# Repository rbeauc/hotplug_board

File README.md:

# hotplug_board
Lab board used for hot insertion of battery cells

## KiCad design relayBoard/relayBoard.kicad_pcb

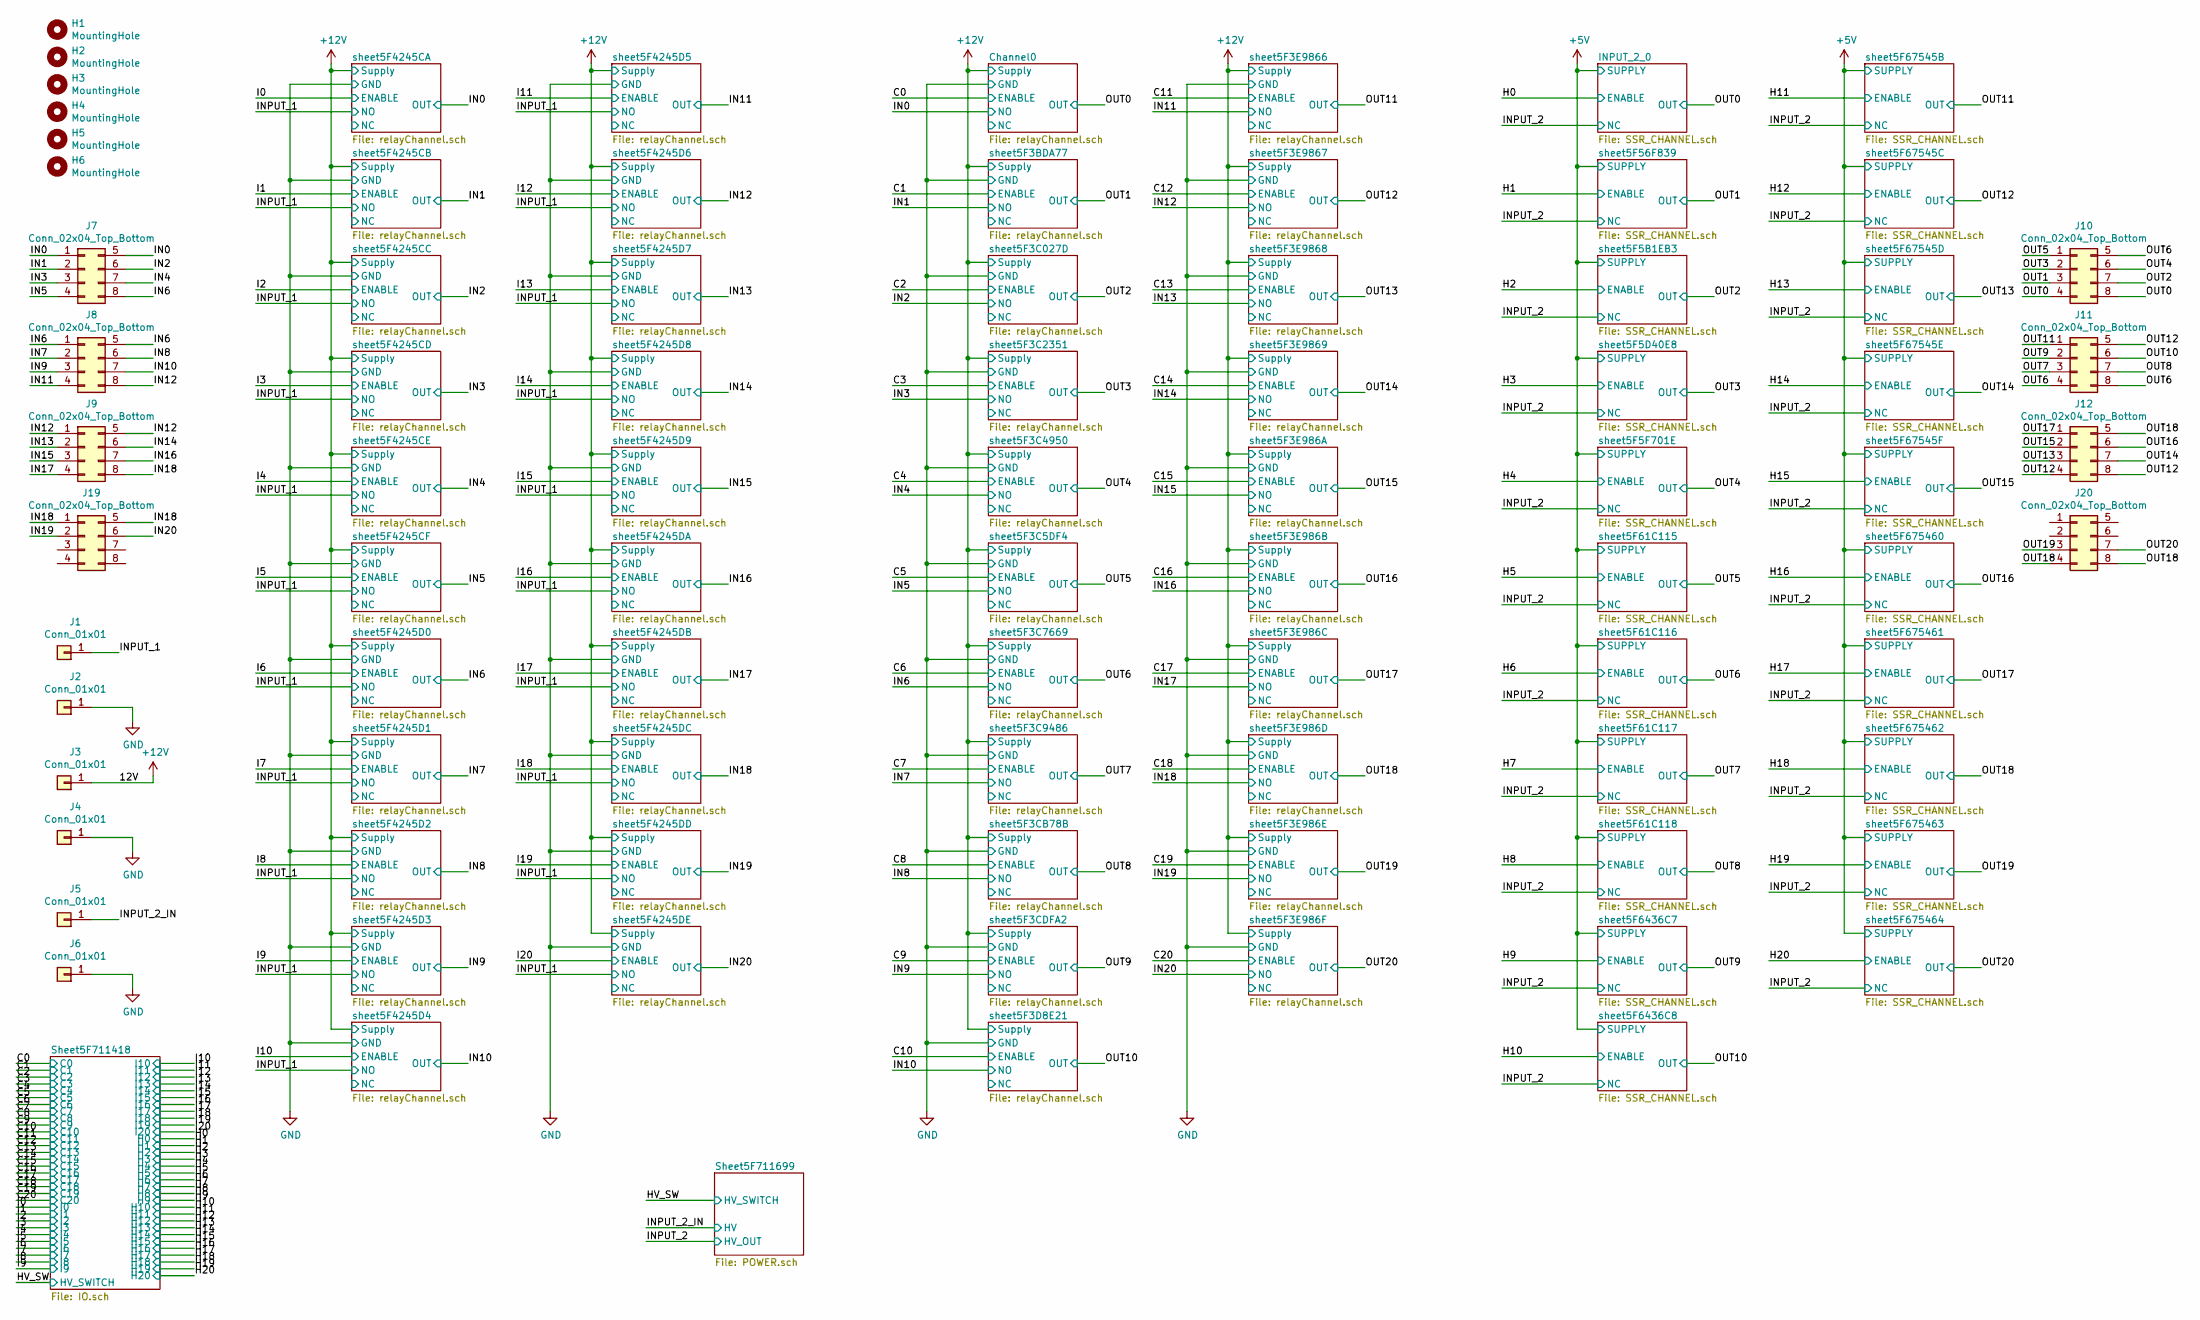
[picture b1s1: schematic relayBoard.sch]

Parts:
H1, H2, H3, H4, H5, H6: MountingHole; MountingHole_5mm
J1, J2, J3, J4, J5, J6: Conn_01x01; Banana_Jack_1Pin
J7, J8, J9, J10, J11, J12, J19, J20: Conn_02x04_Top_Bottom; Molex_Micro-Fit_3.0_43045-0800_2x04_P3.00mm_Horizontal

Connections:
+12V: J3.1; also elsewhere on the board
/IN0: J7.1, J7.5; also elsewhere on the board
/IN1: J7.2; also elsewhere on the board
/IN2: J7.6; also elsewhere on the board
/IN3: J7.3; also elsewhere on the board
/IN4: J7.7; also elsewhere on the board
/IN5: J7.4; also elsewhere on the board
/IN6: J7.8, J8.1, J8.5; also elsewhere on the board
/IN7: J8.2; also elsewhere on the board
/IN8: J8.6; also elsewhere on the board
/IN9: J8.3; also elsewhere on the board
/IN10: J8.7; also elsewhere on the board
/IN11: J8.4; also elsewhere on the board
/IN12: J8.8, J9.1, J9.5; also elsewhere on the board
/IN13: J9.2; also elsewhere on the board
/IN14: J9.6; also elsewhere on the board
/IN15: J9.3; also elsewhere on the board
/IN16: J9.7; also elsewhere on the board
/IN17: J9.4; also elsewhere on the board
/IN18: J9.8, J19.1, J19.5; also elsewhere on the board
/IN19: J19.2; also elsewhere on the board
/IN20: J19.6; also elsewhere on the board
/INPUT_1: J1.1; also elsewhere on the board
/INPUT_2_IN: J5.1; also elsewhere on the board
/OUT0: J10.4, J10.8; also elsewhere on the board
/OUT1: J10.3; also elsewhere on the board
/OUT2: J10.7; also elsewhere on the board
/OUT3: J10.2; also elsewhere on the board
/OUT4: J10.6; also elsewhere on the board
/OUT5: J10.1; also elsewhere on the board
/OUT6: J10.5, J11.4, J11.8; also elsewhere on the board
/OUT7: J11.3; also elsewhere on the board
/OUT8: J11.7; also elsewhere on the board
/OUT9: J11.2; also elsewhere on the board
/OUT10: J11.6; also elsewhere on the board
/OUT11: J11.1; also elsewhere on the board
/OUT12: J11.5, J12.4, J12.8; also elsewhere on the board
/OUT13: J12.3; also elsewhere on the board
/OUT14: J12.7; also elsewhere on the board
/OUT15: J12.2; also elsewhere on the board
/OUT16: J12.6; also elsewhere on the board
/OUT17: J12.1; also elsewhere on the board
/OUT18: J12.5, J20.4, J20.8; also elsewhere on the board
/OUT19: J20.3; also elsewhere on the board
/OUT20: J20.7; also elsewhere on the board
GND: J2.1, J4.1, J6.1; also elsewhere on the board

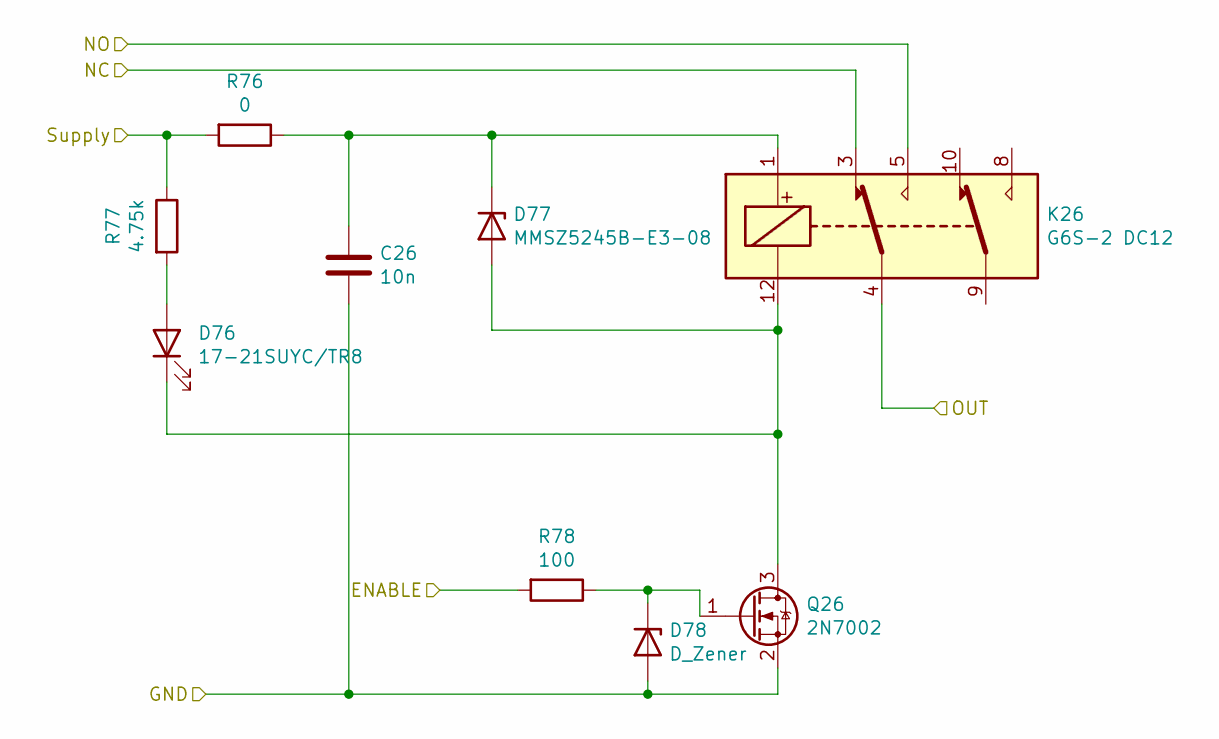
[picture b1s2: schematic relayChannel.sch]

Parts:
C1: 10n; R_0603_1608Metric
D1: 17-21SUYC/TR8; R_0805_2012Metric
D2: MMSZ5245B-E3-08; D_SOD-123
D3: D_Zener; D_0805_2012Metric
K1: G6S-2 DC12; Relay_DPDT_Omron_G6SK-2
Q1: 2N7002; SOT-23
R1: 0; R_0603_1608Metric
R2: 4.75k; R_0603_1608Metric
R3: 100; R_0603_1608Metric

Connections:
+12V: R1.2, R2.1; also elsewhere on the board
/C0: R3.2; also elsewhere on the board
/Channel0/NC: K1.3
/IN0: K1.5; also elsewhere on the board
/OUT0: K1.4; also elsewhere on the board
GND: C1.2, D3.2 (A), Q1.2 (S); also elsewhere on the board
unnamed: C1.1, D2.1 (K), K1.1, R1.1
unnamed: D1.1 (K), D2.2 (A), K1.12, Q1.3 (D)
unnamed: D1.2 (A), R2.2
unnamed: D3.1 (K), Q1.1 (G), R3.1

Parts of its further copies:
C2, C3, C4, C5, C6, C7, C8, C9, C10, C11, C12, C13, C14, C15, C16, C17, C18, C19, C20, C21, C22, C23, C24, C25, C26, C27, C28, C29, C30, C31, C32, C33, C34, C35, C36, C37, C38, C39, C40, C41, C42: 10n; R_0603_1608Metric
D4, D7, D10, D13, D16, D19, D22, D25, D28, D31, D34, D37, D40, D43, D46, D49, D52, D55, D58, D61, D64, D67, D70, D73, D76, D79, D82, D85, D88, D91, D94, D97, D100, D103, D106, D109, D112, D115, D118, D121, D124: 17-21SUYC/TR8; R_0805_2012Metric
D5, D8, D11, D14, D17, D20, D23, D26, D29, D32, D35, D38, D41, D44, D47, D50, D53, D56, D59, D62, D65, D68, D71, D74, D77, D80, D83, D86, D89, D92, D95, D98, D101, D104, D107, D110, D113, D116, D119, D122, D125: MMSZ5245B-E3-08; D_SOD-123
D6, D9, D12, D15, D18, D21, D24, D27, D30, D33, D36, D39, D42, D45, D48, D51, D54, D57, D60, D63, D66, D69, D72, D75, D78, D81, D84, D87, D90, D93, D96, D99, D102, D105, D108, D111, D114, D117, D120, D123, D126: D_Zener; D_0805_2012Metric
K2, K3, K4, K5, K6, K7, K8, K9, K10, K11, K12, K13, K14, K15, K16, K17, K18, K19, K20, K21, K22, K23, K24, K25, K26, K27, K28, K29, K30, K31, K32, K33, K34, K35, K36, K37, K38, K39, K40, K41, K42: G6S-2 DC12; Relay_DPDT_Omron_G6SK-2
Q2, Q3, Q4, Q5, Q6, Q7, Q8, Q9, Q10, Q11, Q12, Q13, Q14, Q15, Q16, Q17, Q18, Q19, Q20, Q21, Q22, Q23, Q24, Q25, Q26, Q27, Q28, Q29, Q30, Q31, Q32, Q33, Q34, Q35, Q36, Q37, Q38, Q39, Q40, Q41, Q42: 2N7002; SOT-23
R5, R8, R11, R14, R17, R20, R23, R26, R29, R32, R35, R38, R41, R44, R47, R50, R53, R56, R59, R62, R65, R68, R71, R74, R77, R80, R83, R86, R89, R92, R95, R98, R101, R104, R107, R110, R113, R116, R119, R122, R125: 4.75k; R_0603_1608Metric
R6, R9, R12, R15, R18, R21, R24, R27, R30, R33, R36, R39, R42, R45, R48, R51, R54, R57, R60, R63, R66, R69, R72, R75, R78, R81, R84, R87, R90, R93, R96, R99, R102, R105, R108, R111, R114, R117, R120, R123, R126: 100; R_0603_1608Metric

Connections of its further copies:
+12V: R5.1, R8.1, R11.1, R14.1, R17.1, R20.1, R23.1, R26.1, R29.1, R32.1, R35.1, R38.1, R41.1, R44.1, R47.1, R50.1, R53.1, R56.1, R59.1, R62.1, R65.1, R68.1, R71.1, R74.1, R77.1, R80.1, R83.1, R86.1, R89.1, R92.1, R95.1, R98.1, R101.1, R104.1, R107.1, R110.1, R113.1, R116.1, R119.1, R122.1, R125.1; also elsewhere on the board
/C1: R6.2; also elsewhere on the board
/C2: R9.2; also elsewhere on the board
/C3: R12.2; also elsewhere on the board
/C4: R15.2; also elsewhere on the board
/C5: R18.2; also elsewhere on the board
/C6: R21.2; also elsewhere on the board
/C7: R24.2; also elsewhere on the board
/C8: R27.2; also elsewhere on the board
/C9: R30.2; also elsewhere on the board
/C10: R33.2; also elsewhere on the board
/C11: R36.2; also elsewhere on the board
/C12: R39.2; also elsewhere on the board
/C13: R42.2; also elsewhere on the board
/C14: R45.2; also elsewhere on the board
/C15: R48.2; also elsewhere on the board
/C16: R51.2; also elsewhere on the board
/C17: R54.2; also elsewhere on the board
/C18: R57.2; also elsewhere on the board
/C19: R60.2; also elsewhere on the board
/C20: R63.2; also elsewhere on the board
/I0: R66.2; also elsewhere on the board
/I1: R69.2; also elsewhere on the board
/I2: R72.2; also elsewhere on the board
/I3: R75.2; also elsewhere on the board
/I4: R78.2; also elsewhere on the board
/I5: R81.2; also elsewhere on the board
/I6: R84.2; also elsewhere on the board
/I7: R87.2; also elsewhere on the board
/I8: R90.2; also elsewhere on the board
/I9: R93.2; also elsewhere on the board
/I10: R96.2; also elsewhere on the board
/I11: R99.2; also elsewhere on the board
/I12: R102.2; also elsewhere on the board
/I13: R105.2; also elsewhere on the board
/I14: R108.2; also elsewhere on the board
/I15: R111.2; also elsewhere on the board
/I16: R114.2; also elsewhere on the board
/I17: R117.2; also elsewhere on the board
/I18: R120.2; also elsewhere on the board
/I19: R123.2; also elsewhere on the board
/I20: R126.2; also elsewhere on the board
/IN0: K22.4; also elsewhere on the board
/IN1: K2.5, K23.4; also elsewhere on the board
/IN2: K3.5, K24.4; also elsewhere on the board
/IN3: K4.5, K25.4; also elsewhere on the board
/IN4: K5.5, K26.4; also elsewhere on the board
/IN5: K6.5, K27.4; also elsewhere on the board
/IN6: K7.5, K28.4; also elsewhere on the board
/IN7: K8.5, K29.4; also elsewhere on the board
/IN8: K9.5, K30.4; also elsewhere on the board
/IN9: K10.5, K31.4; also elsewhere on the board
/IN10: K11.5, K32.4; also elsewhere on the board
/IN11: K12.5, K33.4; also elsewhere on the board
/IN12: K13.5, K34.4; also elsewhere on the board
/IN13: K14.5, K35.4; also elsewhere on the board
/IN14: K15.5, K36.4; also elsewhere on the board
/IN15: K16.5, K37.4; also elsewhere on the board
/IN16: K17.5, K38.4; also elsewhere on the board
/IN17: K18.5, K39.4; also elsewhere on the board
/IN18: K19.5, K40.4; also elsewhere on the board
/IN19: K20.5, K41.4; also elsewhere on the board
/IN20: K21.5, K42.4; also elsewhere on the board
/INPUT_1: K22.5, K23.5, K24.5, K25.5, K26.5, K27.5, K28.5, K29.5, K30.5, K31.5, K32.5, K33.5, K34.5, K35.5, K36.5, K37.5, K38.5, K39.5, K40.5, K41.5, K42.5; also elsewhere on the board
/OUT1: K2.4; also elsewhere on the board
/OUT2: K3.4; also elsewhere on the board
/OUT3: K4.4; also elsewhere on the board
/OUT4: K5.4; also elsewhere on the board
/OUT5: K6.4; also elsewhere on the board
/OUT6: K7.4; also elsewhere on the board
/OUT7: K8.4; also elsewhere on the board
/OUT8: K9.4; also elsewhere on the board
/OUT9: K10.4; also elsewhere on the board
/OUT10: K11.4; also elsewhere on the board
/OUT11: K12.4; also elsewhere on the board
/OUT12: K13.4; also elsewhere on the board
/OUT13: K14.4; also elsewhere on the board
/OUT14: K15.4; also elsewhere on the board
/OUT15: K16.4; also elsewhere on the board
/OUT16: K17.4; also elsewhere on the board
/OUT17: K18.4; also elsewhere on the board
/OUT18: K19.4; also elsewhere on the board
/OUT19: K20.4; also elsewhere on the board
/OUT20: K21.4; also elsewhere on the board
/sheet5F3BDA77/NC: K2.3
/sheet5F3C5DF4/NC: K6.3
/sheet5F3C027D/NC: K3.3
/sheet5F3C2351/NC: K4.3
/sheet5F3C4950/NC: K5.3
/sheet5F3C7669/NC: K7.3
/sheet5F3C9486/NC: K8.3
/sheet5F3CB78B/NC: K9.3
/sheet5F3CDFA2/NC: K10.3
/sheet5F3D8E21/NC: K11.3
/sheet5F3E986A/NC: K16.3
/sheet5F3E986B/NC: K17.3
/sheet5F3E986C/NC: K18.3
/sheet5F3E986D/NC: K19.3
/sheet5F3E986E/NC: K20.3
/sheet5F3E986F/NC: K21.3
/sheet5F3E9866/NC: K12.3
/sheet5F3E9867/NC: K13.3
/sheet5F3E9868/NC: K14.3
/sheet5F3E9869/NC: K15.3
/sheet5F4245CA/NC: K22.3
/sheet5F4245CB/NC: K23.3
/sheet5F4245CC/NC: K24.3
/sheet5F4245CD/NC: K25.3
/sheet5F4245CE/NC: K26.3
/sheet5F4245CF/NC: K27.3
/sheet5F4245D0/NC: K28.3
/sheet5F4245D1/NC: K29.3
/sheet5F4245D2/NC: K30.3
/sheet5F4245D3/NC: K31.3
/sheet5F4245D4/NC: K32.3
/sheet5F4245D5/NC: K33.3
/sheet5F4245D6/NC: K34.3
/sheet5F4245D7/NC: K35.3
/sheet5F4245D8/NC: K36.3
/sheet5F4245D9/NC: K37.3
/sheet5F4245DA/NC: K38.3
/sheet5F4245DB/NC: K39.3
/sheet5F4245DC/NC: K40.3
/sheet5F4245DD/NC: K41.3
/sheet5F4245DE/NC: K42.3
GND: C2.2, C3.2, C4.2, C5.2, C6.2, C7.2, C8.2, C9.2, C10.2, C11.2, C12.2, C13.2, C14.2, C15.2, C16.2, C17.2, C18.2, C19.2, C20.2, C21.2, C22.2, C23.2, C24.2, C25.2, C26.2, C27.2, C28.2, C29.2, C30.2, C31.2, C32.2, C33.2, C34.2, C35.2, C36.2, C37.2, C38.2, C39.2, C40.2, C41.2, C42.2, D6.2 (A), D9.2 (A), D12.2 (A), D15.2 (A), D18.2 (A), D21.2 (A), D24.2 (A), D27.2 (A), D30.2 (A), D33.2 (A), D36.2 (A), D39.2 (A), D42.2 (A), D45.2 (A), D48.2 (A), D51.2 (A), D54.2 (A), D57.2 (A), D60.2 (A), D63.2 (A), D66.2 (A), D69.2 (A), D72.2 (A), D75.2 (A), D78.2 (A), D81.2 (A), D84.2 (A), D87.2 (A), D90.2 (A), D93.2 (A), D96.2 (A), D99.2 (A), D102.2 (A), D105.2 (A), D108.2 (A), D111.2 (A), D114.2 (A), D117.2 (A), D120.2 (A), D123.2 (A), D126.2 (A), Q2.2 (S), Q3.2 (S), Q4.2 (S), Q5.2 (S), Q6.2 (S), Q7.2 (S), Q8.2 (S), Q9.2 (S), Q10.2 (S), Q11.2 (S), Q12.2 (S), Q13.2 (S), Q14.2 (S), Q15.2 (S), Q16.2 (S), Q17.2 (S), Q18.2 (S), Q19.2 (S), Q20.2 (S), Q21.2 (S), Q22.2 (S), Q23.2 (S), Q24.2 (S), Q25.2 (S), Q26.2 (S), Q27.2 (S), Q28.2 (S), Q29.2 (S), Q30.2 (S), Q31.2 (S), Q32.2 (S), Q33.2 (S), Q34.2 (S), Q35.2 (S), Q36.2 (S), Q37.2 (S), Q38.2 (S), Q39.2 (S), Q40.2 (S), Q41.2 (S), Q42.2 (S); also elsewhere on the board
unnamed 162: C2.1, D5.1 (K), K2.1; also elsewhere on the board
unnamed 163: C3.1, D8.1 (K), K3.1; also elsewhere on the board
unnamed 164: C4.1, D11.1 (K), K4.1; also elsewhere on the board
unnamed 165: C5.1, D14.1 (K), K5.1; also elsewhere on the board
unnamed 166: C6.1, D17.1 (K), K6.1; also elsewhere on the board
unnamed 167: C7.1, D20.1 (K), K7.1; also elsewhere on the board
unnamed 168: C8.1, D23.1 (K), K8.1; also elsewhere on the board
unnamed 169: C9.1, D26.1 (K), K9.1; also elsewhere on the board
unnamed 170: C10.1, D29.1 (K), K10.1; also elsewhere on the board
unnamed 171: C11.1, D32.1 (K), K11.1; also elsewhere on the board
unnamed 172: C12.1, D35.1 (K), K12.1; also elsewhere on the board
unnamed 173: C13.1, D38.1 (K), K13.1; also elsewhere on the board
unnamed 174: C14.1, D41.1 (K), K14.1; also elsewhere on the board
unnamed 175: C15.1, D44.1 (K), K15.1; also elsewhere on the board
unnamed 176: C16.1, D47.1 (K), K16.1; also elsewhere on the board
unnamed 177: C17.1, D50.1 (K), K17.1; also elsewhere on the board
unnamed 178: C18.1, D53.1 (K), K18.1; also elsewhere on the board
unnamed 179: C19.1, D56.1 (K), K19.1; also elsewhere on the board
unnamed 180: C20.1, D59.1 (K), K20.1; also elsewhere on the board
unnamed 181: C21.1, D62.1 (K), K21.1; also elsewhere on the board
unnamed 182: C22.1, D65.1 (K), K22.1; also elsewhere on the board
unnamed 183: C23.1, D68.1 (K), K23.1; also elsewhere on the board
unnamed 184: C24.1, D71.1 (K), K24.1; also elsewhere on the board
unnamed 185: C25.1, D74.1 (K), K25.1; also elsewhere on the board
unnamed 186: C26.1, D77.1 (K), K26.1; also elsewhere on the board
unnamed 187: C27.1, D80.1 (K), K27.1; also elsewhere on the board
unnamed 188: C28.1, D83.1 (K), K28.1; also elsewhere on the board
unnamed 189: C29.1, D86.1 (K), K29.1; also elsewhere on the board
unnamed 190: C30.1, D89.1 (K), K30.1; also elsewhere on the board
unnamed 191: C31.1, D92.1 (K), K31.1; also elsewhere on the board
unnamed 192: C32.1, D95.1 (K), K32.1; also elsewhere on the board
unnamed 193: C33.1, D98.1 (K), K33.1; also elsewhere on the board
unnamed 194: C34.1, D101.1 (K), K34.1; also elsewhere on the board
unnamed 195: C35.1, D104.1 (K), K35.1; also elsewhere on the board
unnamed 196: C36.1, D107.1 (K), K36.1; also elsewhere on the board
unnamed 197: C37.1, D110.1 (K), K37.1; also elsewhere on the board
unnamed 198: C38.1, D113.1 (K), K38.1; also elsewhere on the board
unnamed 199: C39.1, D116.1 (K), K39.1; also elsewhere on the board
unnamed 200: C40.1, D119.1 (K), K40.1; also elsewhere on the board
unnamed 201: C41.1, D122.1 (K), K41.1; also elsewhere on the board
unnamed 202: C42.1, D125.1 (K), K42.1; also elsewhere on the board
unnamed: D4.1 (K), D5.2 (A), K2.12, Q2.3 (D)
unnamed: D4.2 (A), R5.2
unnamed: D6.1 (K), Q2.1 (G), R6.1
unnamed: D7.1 (K), D8.2 (A), K3.12, Q3.3 (D)
unnamed: D7.2 (A), R8.2
unnamed: D9.1 (K), Q3.1 (G), R9.1
unnamed: D10.1 (K), D11.2 (A), K4.12, Q4.3 (D)
unnamed: D10.2 (A), R11.2
unnamed: D12.1 (K), Q4.1 (G), R12.1
unnamed: D13.1 (K), D14.2 (A), K5.12, Q5.3 (D)
unnamed: D13.2 (A), R14.2
unnamed: D15.1 (K), Q5.1 (G), R15.1
unnamed: D16.1 (K), D17.2 (A), K6.12, Q6.3 (D)
unnamed: D16.2 (A), R17.2
unnamed: D18.1 (K), Q6.1 (G), R18.1
unnamed: D19.1 (K), D20.2 (A), K7.12, Q7.3 (D)
unnamed: D19.2 (A), R20.2
unnamed: D21.1 (K), Q7.1 (G), R21.1
unnamed: D22.1 (K), D23.2 (A), K8.12, Q8.3 (D)
unnamed: D22.2 (A), R23.2
unnamed: D24.1 (K), Q8.1 (G), R24.1
unnamed: D25.1 (K), D26.2 (A), K9.12, Q9.3 (D)
unnamed: D25.2 (A), R26.2
unnamed: D27.1 (K), Q9.1 (G), R27.1
unnamed: D28.1 (K), D29.2 (A), K10.12, Q10.3 (D)
unnamed: D28.2 (A), R29.2
unnamed: D30.1 (K), Q10.1 (G), R30.1
unnamed: D31.1 (K), D32.2 (A), K11.12, Q11.3 (D)
unnamed: D31.2 (A), R32.2
unnamed: D33.1 (K), Q11.1 (G), R33.1
unnamed: D34.1 (K), D35.2 (A), K12.12, Q12.3 (D)
unnamed: D34.2 (A), R35.2
unnamed: D36.1 (K), Q12.1 (G), R36.1
unnamed: D37.1 (K), D38.2 (A), K13.12, Q13.3 (D)
unnamed: D37.2 (A), R38.2
unnamed: D39.1 (K), Q13.1 (G), R39.1
unnamed: D40.1 (K), D41.2 (A), K14.12, Q14.3 (D)
unnamed: D40.2 (A), R41.2
unnamed: D42.1 (K), Q14.1 (G), R42.1
unnamed: D43.1 (K), D44.2 (A), K15.12, Q15.3 (D)
unnamed: D43.2 (A), R44.2
unnamed: D45.1 (K), Q15.1 (G), R45.1
unnamed: D46.1 (K), D47.2 (A), K16.12, Q16.3 (D)
unnamed: D46.2 (A), R47.2
unnamed: D48.1 (K), Q16.1 (G), R48.1
unnamed: D49.1 (K), D50.2 (A), K17.12, Q17.3 (D)
unnamed: D49.2 (A), R50.2
unnamed: D51.1 (K), Q17.1 (G), R51.1
unnamed: D52.1 (K), D53.2 (A), K18.12, Q18.3 (D)
unnamed: D52.2 (A), R53.2
unnamed: D54.1 (K), Q18.1 (G), R54.1
unnamed: D55.1 (K), D56.2 (A), K19.12, Q19.3 (D)
unnamed: D55.2 (A), R56.2
unnamed: D57.1 (K), Q19.1 (G), R57.1
unnamed: D58.1 (K), D59.2 (A), K20.12, Q20.3 (D)
unnamed: D58.2 (A), R59.2
unnamed: D60.1 (K), Q20.1 (G), R60.1
unnamed: D61.1 (K), D62.2 (A), K21.12, Q21.3 (D)
unnamed: D61.2 (A), R62.2
unnamed: D63.1 (K), Q21.1 (G), R63.1
unnamed: D64.1 (K), D65.2 (A), K22.12, Q22.3 (D)
unnamed: D64.2 (A), R65.2
unnamed: D66.1 (K), Q22.1 (G), R66.1
unnamed: D67.1 (K), D68.2 (A), K23.12, Q23.3 (D)
unnamed: D67.2 (A), R68.2
unnamed: D69.1 (K), Q23.1 (G), R69.1
unnamed: D70.1 (K), D71.2 (A), K24.12, Q24.3 (D)
unnamed: D70.2 (A), R71.2
unnamed: D72.1 (K), Q24.1 (G), R72.1
unnamed: D73.1 (K), D74.2 (A), K25.12, Q25.3 (D)
unnamed: D73.2 (A), R74.2
unnamed: D75.1 (K), Q25.1 (G), R75.1
unnamed: D76.1 (K), D77.2 (A), K26.12, Q26.3 (D)
unnamed: D76.2 (A), R77.2
unnamed: D78.1 (K), Q26.1 (G), R78.1
unnamed: D79.1 (K), D80.2 (A), K27.12, Q27.3 (D)
unnamed: D79.2 (A), R80.2
unnamed: D81.1 (K), Q27.1 (G), R81.1
unnamed: D82.1 (K), D83.2 (A), K28.12, Q28.3 (D)
unnamed: D82.2 (A), R83.2
unnamed: D84.1 (K), Q28.1 (G), R84.1
unnamed: D85.1 (K), D86.2 (A), K29.12, Q29.3 (D)
unnamed: D85.2 (A), R86.2
unnamed: D87.1 (K), Q29.1 (G), R87.1
unnamed: D88.1 (K), D89.2 (A), K30.12, Q30.3 (D)
unnamed: D88.2 (A), R89.2
unnamed: D90.1 (K), Q30.1 (G), R90.1
unnamed: D91.1 (K), D92.2 (A), K31.12, Q31.3 (D)
unnamed: D91.2 (A), R92.2
unnamed: D93.1 (K), Q31.1 (G), R93.1
unnamed: D94.1 (K), D95.2 (A), K32.12, Q32.3 (D)
unnamed: D94.2 (A), R95.2
unnamed: D96.1 (K), Q32.1 (G), R96.1
unnamed: D97.1 (K), D98.2 (A), K33.12, Q33.3 (D)
unnamed: D97.2 (A), R98.2
unnamed: D99.1 (K), Q33.1 (G), R99.1
unnamed: D100.1 (K), D101.2 (A), K34.12, Q34.3 (D)
unnamed: D100.2 (A), R101.2
unnamed: D102.1 (K), Q34.1 (G), R102.1
unnamed: D103.1 (K), D104.2 (A), K35.12, Q35.3 (D)
unnamed: D103.2 (A), R104.2
unnamed: D105.1 (K), Q35.1 (G), R105.1
unnamed: D106.1 (K), D107.2 (A), K36.12, Q36.3 (D)
unnamed: D106.2 (A), R107.2
unnamed: D108.1 (K), Q36.1 (G), R108.1
unnamed: D109.1 (K), D110.2 (A), K37.12, Q37.3 (D)
unnamed: D109.2 (A), R110.2
unnamed: D111.1 (K), Q37.1 (G), R111.1
unnamed: D112.1 (K), D113.2 (A), K38.12, Q38.3 (D)
unnamed: D112.2 (A), R113.2
unnamed: D114.1 (K), Q38.1 (G), R114.1
unnamed: D115.1 (K), D116.2 (A), K39.12, Q39.3 (D)
unnamed: D115.2 (A), R116.2
unnamed: D117.1 (K), Q39.1 (G), R117.1
unnamed: D118.1 (K), D119.2 (A), K40.12, Q40.3 (D)
unnamed: D118.2 (A), R119.2
unnamed: D120.1 (K), Q40.1 (G), R120.1
unnamed: D121.1 (K), D122.2 (A), K41.12, Q41.3 (D)
unnamed: D121.2 (A), R122.2
unnamed: D123.1 (K), Q41.1 (G), R123.1
unnamed: D124.1 (K), D125.2 (A), K42.12, Q42.3 (D)
unnamed: D124.2 (A), R125.2
unnamed: D126.1 (K), Q42.1 (G), R126.1

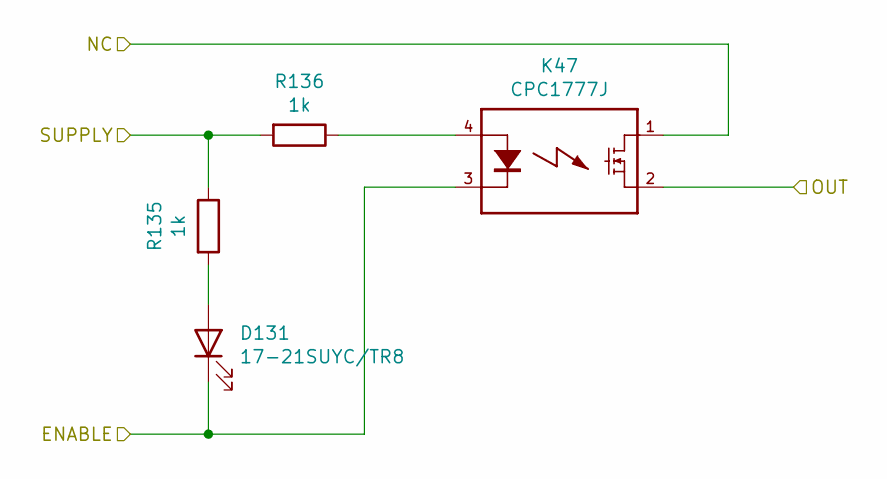
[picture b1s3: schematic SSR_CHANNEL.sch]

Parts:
D127: 17-21SUYC/TR8; R_0805_2012Metric
K43: CPC1777J; TO381P2016X515X2916-4
R127, R128: 1k; R_0603_1608Metric

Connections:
+5V: R127.1, R128.2; also elsewhere on the board
/H0: D127.1 (K), K43.3; also elsewhere on the board
/OUT0: K43.2; also elsewhere on the board
unnamed: D127.2 (A), R127.2
unnamed: K43.4, R128.1

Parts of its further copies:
D128, D129, D130, D131, D132, D133, D134, D135, D136, D137, D138, D139, D140, D141, D142, D143, D144, D145, D146, D147: 17-21SUYC/TR8; R_0805_2012Metric
K44, K45, K46, K47, K48, K49, K50, K51, K52, K53, K54, K55, K56, K57, K58, K59, K60, K61, K62, K63: CPC1777J; TO381P2016X515X2916-4
R129, R130, R131, R132, R133, R134, R135, R136, R137, R138, R139, R140, R141, R142, R143, R144, R145, R146, R147, R148, R149, R150, R151, R152, R153, R154, R155, R156, R157, R158, R159, R160, R161, R162, R163, R164, R165, R166, R167, R168: 1k; R_0603_1608Metric

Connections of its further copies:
+5V: R129.1, R130.2, R131.1, R132.2, R133.1, R134.2, R135.1, R136.2, R137.1, R138.2, R139.1, R140.2, R141.1, R142.2, R143.1, R144.2, R145.1, R146.2, R147.1, R148.2, R149.1, R150.2, R151.1, R152.2, R153.1, R154.2, R155.1, R156.2, R157.1, R158.2, R159.1, R160.2, R161.1, R162.2, R163.1, R164.2, R165.1, R166.2, R167.1, R168.2; also elsewhere on the board
/H1: D128.1 (K), K44.3; also elsewhere on the board
/H2: D129.1 (K), K45.3; also elsewhere on the board
/H3: D130.1 (K), K46.3; also elsewhere on the board
/H4: D131.1 (K), K47.3; also elsewhere on the board
/H5: D132.1 (K), K48.3; also elsewhere on the board
/H6: D133.1 (K), K49.3; also elsewhere on the board
/H7: D134.1 (K), K50.3; also elsewhere on the board
/H8: D135.1 (K), K51.3; also elsewhere on the board
/H9: D136.1 (K), K52.3; also elsewhere on the board
/H10: D137.1 (K), K53.3; also elsewhere on the board
/H11: D138.1 (K), K54.3; also elsewhere on the board
/H12: D139.1 (K), K55.3; also elsewhere on the board
/H13: D140.1 (K), K56.3; also elsewhere on the board
/H14: D141.1 (K), K57.3; also elsewhere on the board
/H15: D142.1 (K), K58.3; also elsewhere on the board
/H16: D143.1 (K), K59.3; also elsewhere on the board
/H17: D144.1 (K), K60.3; also elsewhere on the board
/H18: D145.1 (K), K61.3; also elsewhere on the board
/H19: D146.1 (K), K62.3; also elsewhere on the board
/H20: D147.1 (K), K63.3; also elsewhere on the board
/OUT1: K44.2; also elsewhere on the board
/OUT2: K45.2; also elsewhere on the board
/OUT3: K46.2; also elsewhere on the board
/OUT4: K47.2; also elsewhere on the board
/OUT5: K48.2; also elsewhere on the board
/OUT6: K49.2; also elsewhere on the board
/OUT7: K50.2; also elsewhere on the board
/OUT8: K51.2; also elsewhere on the board
/OUT9: K52.2; also elsewhere on the board
/OUT10: K53.2; also elsewhere on the board
/OUT11: K54.2; also elsewhere on the board
/OUT12: K55.2; also elsewhere on the board
/OUT13: K56.2; also elsewhere on the board
/OUT14: K57.2; also elsewhere on the board
/OUT15: K58.2; also elsewhere on the board
/OUT16: K59.2; also elsewhere on the board
/OUT17: K60.2; also elsewhere on the board
/OUT18: K61.2; also elsewhere on the board
/OUT19: K62.2; also elsewhere on the board
/OUT20: K63.2; also elsewhere on the board
unnamed: D128.2 (A), R129.2
unnamed: D129.2 (A), R131.2
unnamed: D130.2 (A), R133.2
unnamed: D131.2 (A), R135.2
unnamed: D132.2 (A), R137.2
unnamed: D133.2 (A), R139.2
unnamed: D134.2 (A), R141.2
unnamed: D135.2 (A), R143.2
unnamed: D136.2 (A), R145.2
unnamed: D137.2 (A), R147.2
unnamed: D138.2 (A), R149.2
unnamed: D139.2 (A), R151.2
unnamed: D140.2 (A), R153.2
unnamed: D141.2 (A), R155.2
unnamed: D142.2 (A), R157.2
unnamed: D143.2 (A), R159.2
unnamed: D144.2 (A), R161.2
unnamed: D145.2 (A), R163.2
unnamed: D146.2 (A), R165.2
unnamed: D147.2 (A), R167.2
unnamed: K44.4, R130.1
unnamed: K45.4, R132.1
unnamed: K46.4, R134.1
unnamed: K47.4, R136.1
unnamed: K48.4, R138.1
unnamed: K49.4, R140.1
unnamed: K50.4, R142.1
unnamed: K51.4, R144.1
unnamed: K52.4, R146.1
unnamed: K53.4, R148.1
unnamed: K54.4, R150.1
unnamed: K55.4, R152.1
unnamed: K56.4, R154.1
unnamed: K57.4, R156.1
unnamed: K58.4, R158.1
unnamed: K59.4, R160.1
unnamed: K60.4, R162.1
unnamed: K61.4, R164.1
unnamed: K62.4, R166.1
unnamed: K63.4, R168.1

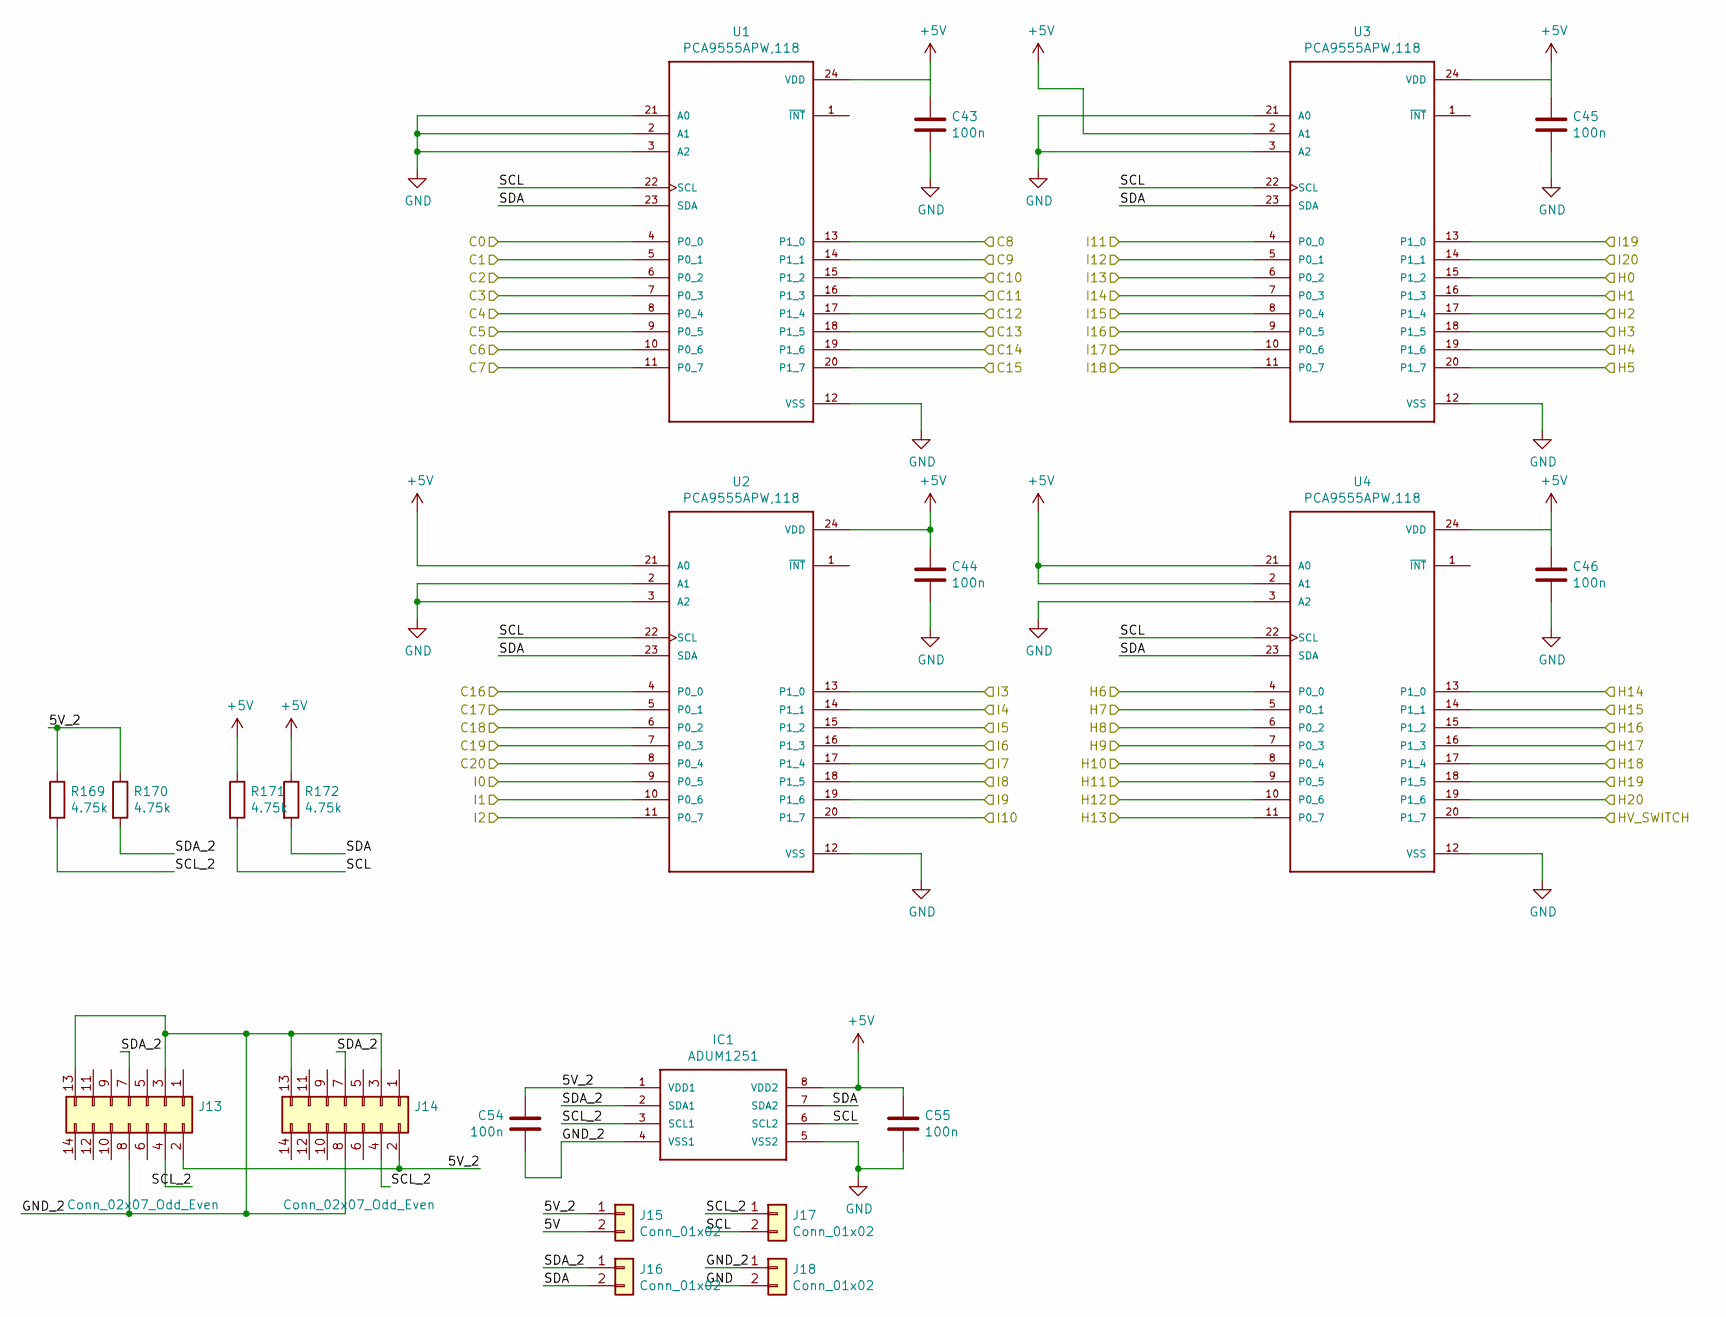
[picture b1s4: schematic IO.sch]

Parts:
C43, C44, C45, C46, C54, C55: 100n; R_0603_1608Metric
IC1: ADUM1251; SO08
J13, J14: Conn_02x07_Odd_Even; PinHeader_2x07_P2.00mm_Vertical
J15, J16, J17, J18: Conn_01x02; PinHeader_1x02_P2.00mm_Vertical
R169, R170, R171, R172: 4.75k; R_0603_1608Metric
U1, U2, U3, U4: PCA9555APW,118; SOP65P640X110-24N

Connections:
+5V: C43.1, C44.1, C45.1, C46.1, C55.1, IC1.8 (VDD2), R171.1, R172.1, U1.24 (VDD), U2.21 (A0), U2.24 (VDD), U3.2 (A1), U3.24 (VDD), U4.2 (A1), U4.21 (A0), U4.24 (VDD); also elsewhere on the board
/C0: U1.4 (P0_0); also elsewhere on the board
/C1: U1.5 (P0_1); also elsewhere on the board
/C2: U1.6 (P0_2); also elsewhere on the board
/C3: U1.7 (P0_3); also elsewhere on the board
/C4: U1.8 (P0_4); also elsewhere on the board
/C5: U1.9 (P0_5); also elsewhere on the board
/C6: U1.10 (P0_6); also elsewhere on the board
/C7: U1.11 (P0_7); also elsewhere on the board
/C8: U1.13 (P1_0); also elsewhere on the board
/C9: U1.14 (P1_1); also elsewhere on the board
/C10: U1.15 (P1_2); also elsewhere on the board
/C11: U1.16 (P1_3); also elsewhere on the board
/C12: U1.17 (P1_4); also elsewhere on the board
/C13: U1.18 (P1_5); also elsewhere on the board
/C14: U1.19 (P1_6); also elsewhere on the board
/C15: U1.20 (P1_7); also elsewhere on the board
/C16: U2.4 (P0_0); also elsewhere on the board
/C17: U2.5 (P0_1); also elsewhere on the board
/C18: U2.6 (P0_2); also elsewhere on the board
/C19: U2.7 (P0_3); also elsewhere on the board
/C20: U2.8 (P0_4); also elsewhere on the board
/H0: U3.15 (P1_2); also elsewhere on the board
/H1: U3.16 (P1_3); also elsewhere on the board
/H2: U3.17 (P1_4); also elsewhere on the board
/H3: U3.18 (P1_5); also elsewhere on the board
/H4: U3.19 (P1_6); also elsewhere on the board
/H5: U3.20 (P1_7); also elsewhere on the board
/H6: U4.4 (P0_0); also elsewhere on the board
/H7: U4.5 (P0_1); also elsewhere on the board
/H8: U4.6 (P0_2); also elsewhere on the board
/H9: U4.7 (P0_3); also elsewhere on the board
/H10: U4.8 (P0_4); also elsewhere on the board
/H11: U4.9 (P0_5); also elsewhere on the board
/H12: U4.10 (P0_6); also elsewhere on the board
/H13: U4.11 (P0_7); also elsewhere on the board
/H14: U4.13 (P1_0); also elsewhere on the board
/H15: U4.14 (P1_1); also elsewhere on the board
/H16: U4.15 (P1_2); also elsewhere on the board
/H17: U4.16 (P1_3); also elsewhere on the board
/H18: U4.17 (P1_4); also elsewhere on the board
/H19: U4.18 (P1_5); also elsewhere on the board
/H20: U4.19 (P1_6); also elsewhere on the board
/HV_SW: U4.20 (P1_7); also elsewhere on the board
/I0: U2.9 (P0_5); also elsewhere on the board
/I1: U2.10 (P0_6); also elsewhere on the board
/I2: U2.11 (P0_7); also elsewhere on the board
/I3: U2.13 (P1_0); also elsewhere on the board
/I4: U2.14 (P1_1); also elsewhere on the board
/I5: U2.15 (P1_2); also elsewhere on the board
/I6: U2.16 (P1_3); also elsewhere on the board
/I7: U2.17 (P1_4); also elsewhere on the board
/I8: U2.18 (P1_5); also elsewhere on the board
/I9: U2.19 (P1_6); also elsewhere on the board
/I10: U2.20 (P1_7); also elsewhere on the board
/I11: U3.4 (P0_0); also elsewhere on the board
/I12: U3.5 (P0_1); also elsewhere on the board
/I13: U3.6 (P0_2); also elsewhere on the board
/I14: U3.7 (P0_3); also elsewhere on the board
/I15: U3.8 (P0_4); also elsewhere on the board
/I16: U3.9 (P0_5); also elsewhere on the board
/I17: U3.10 (P0_6); also elsewhere on the board
/I18: U3.11 (P0_7); also elsewhere on the board
/I19: U3.13 (P1_0); also elsewhere on the board
/I20: U3.14 (P1_1); also elsewhere on the board
/Sheet5F711418/5V: J15.2
/Sheet5F711418/5V_2: C54.1, IC1.1 (VDD1), J13.2, J14.2, J15.1, R169.1, R170.1
/Sheet5F711418/GND_2: C54.2, IC1.4 (VSS1), J13.3, J13.8, J13.13, J14.3, J14.8, J14.13, J18.1
/Sheet5F711418/SCL: IC1.6 (SCL2), J17.2, R171.2, U1.22 (SCL), U2.22 (SCL), U3.22 (SCL), U4.22 (SCL)
/Sheet5F711418/SCL_2: IC1.3 (SCL1), J13.4, J14.4, J17.1, R169.2
/Sheet5F711418/SDA: IC1.7 (SDA2), J16.2, R172.2, U1.23 (SDA), U2.23 (SDA), U3.23 (SDA), U4.23 (SDA)
/Sheet5F711418/SDA_2: IC1.2 (SDA1), J13.7, J14.7, J16.1, R170.2
GND: C43.2, C44.2, C45.2, C46.2, C55.2, IC1.5 (VSS2), J18.2, U1.2 (A1), U1.3 (A2), U1.12 (VSS), U1.21 (A0), U2.2 (A1), U2.3 (A2), U2.12 (VSS), U3.3 (A2), U3.12 (VSS), U3.21 (A0), U4.3 (A2), U4.12 (VSS); also elsewhere on the board
